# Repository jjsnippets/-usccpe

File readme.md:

# BSCPE USC Code Compilation

This repository cotains all the code and laboratory exercises that I did throughout my Bachelor of Computer Engineering Degree in the University of San Carlos.

*These were originally in separate repositories, but is merged for the convenience of everyone 😅.*

> **Contains the following subrepositories**:
>
> **CPE 1102L**: PROGRAMMING LOGIC AND DESIGN
> **CPE 1202L**: DATA STRUCTURES AND ALGORITHMS
> **CPE 2101L**: OBJECT ORIENTED PROGRAMMING
> **CPE 2201**: SOFTWARE DESIGN
> **CPE 3101L**: INTRODUCTION TO HDL
> **CPE 3102**: FEEDBACK AND CONTROL SYSTEMS
> **CPE 3103**: FUNDAMENTALS OF MIXED SIGNALS AND SENSORS
> **CPE 3104**: MICROPROCESSORS
> **CPE 3108**: NUMERICAL METHODS
> **CPE 3108**: INFORMATION ENGINEERING 1
> **CPE 3201**: EMBEDDED SYSTEMS
> **CPE 3203**: DIGITAL SIGNAL PROCESSING
> **CPE 3205**: EMERGING TECHNOLOGIES IN CPE
> **CPE 3252**: INFORMATION ENGINEERING 2
>
> Each contains its own brief readme.md.

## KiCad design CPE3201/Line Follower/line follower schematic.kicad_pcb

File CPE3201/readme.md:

# CPE 3201 (EMBEDDED SYSTEMS)
- All code is in C
- Hardware used: PIC16F877A microcontroller
- Compiler used: MPLAB XC8 v1.33

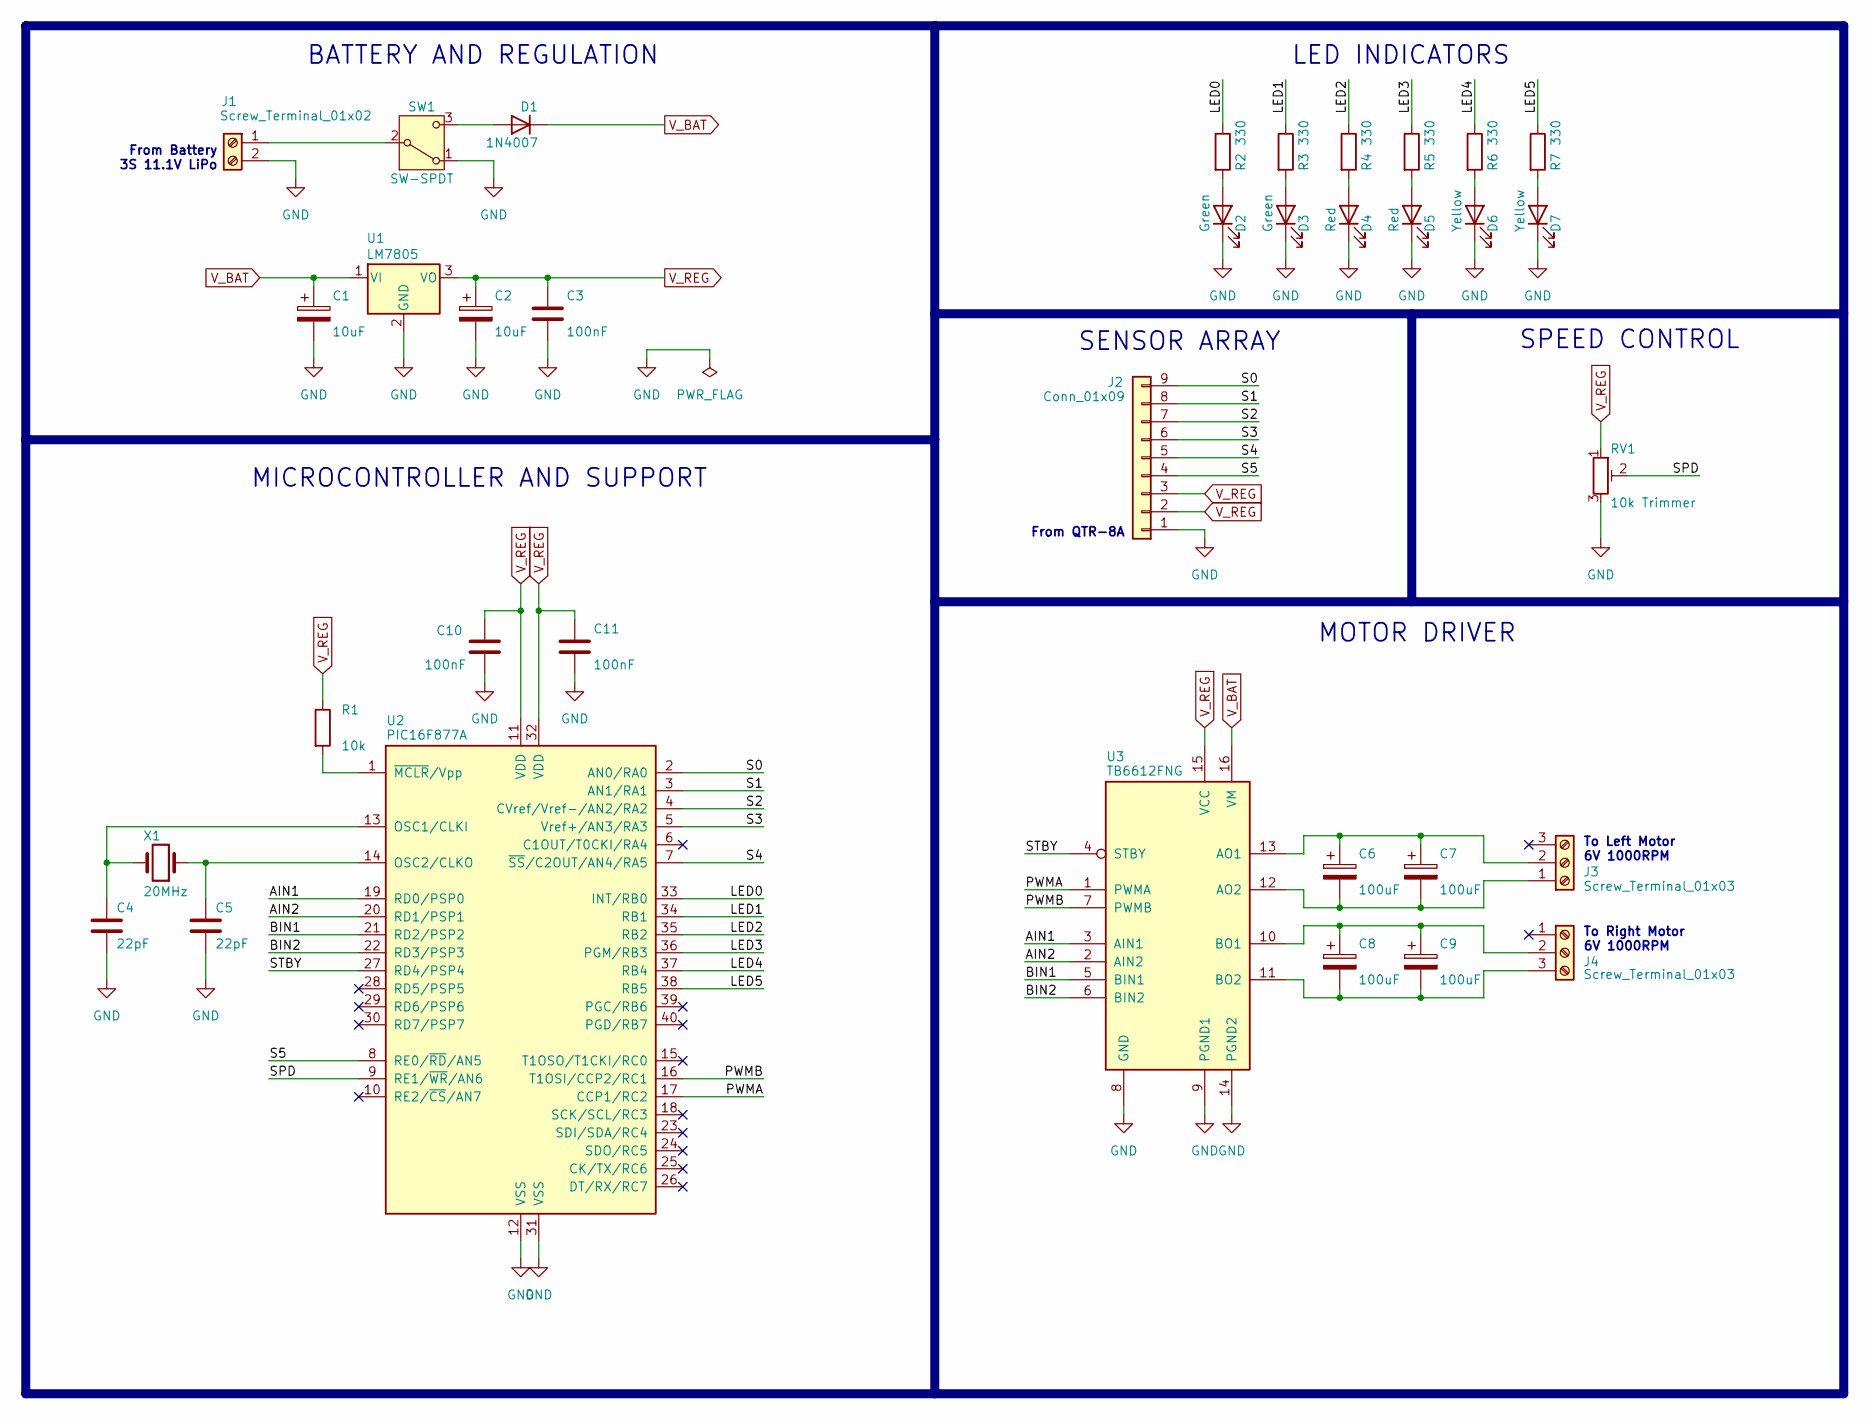
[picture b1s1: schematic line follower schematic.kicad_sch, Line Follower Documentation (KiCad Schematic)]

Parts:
C1, C2: 10uF; CP_Radial_D5.0mm_P2.50mm
C3, C10, C11: 100nF; C_Disc_D5.1mm_W3.2mm_P5.00mm
C4, C5: 22pF; C_Disc_D5.1mm_W3.2mm_P5.00mm
C6, C7, C8, C9: 100uF; CP_Radial_D6.3mm_P2.50mm
D1: 1N4007; D_DO-41_SOD81_P10.16mm_Horizontal
D2, D3: Green; LED_D5.0mm
D4, D5: Red; LED_D5.0mm
D6, D7: Yellow; LED_D5.0mm
J1: Screw_Terminal_01x02; TerminalBlock_Phoenix_MKDS-1,5-2-5.08_1x02_P5.08mm_Horizont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
J2: Conn_01x09; PinHeader_1x09_P2.54mm_Vertical
J3, J4: Screw_Terminal_01x03; TerminalBlock_Phoenix_MKDS-1,5-3_1x03_P5.00mm_Horizontal
R1: 10k; R_Axial_DIN0207_L6.3mm_D2.5mm_P10.16mm_Horizontal
R2, R3, R4, R5, R6, R7: 330; R_Axial_DIN0207_L6.3mm_D2.5mm_P10.16mm_Horizontal
RV1: 10k Trimmer; Potentiometer_Bourns_3296Y_Vertical
SW1: SW-SPDT; TerminalBlock_Phoenix_MKDS-1,5-3_1x03_P5.00mm_Horizontal
U1: LM7805; TO-220-3_Vertical
U2: PIC16F877A; DIP-40_W15.24mm
U3: TB6612FNG; DIP-16_W7.62mm_LongPads
X1: 20MHz; Crystal_HC49-U_Vertical

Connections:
/AIN1: U2.19 (RD0/PSP0), U3.3 (AIN1)
/AIN2: U2.20 (RD1/PSP1), U3.2 (AIN2)
/BIN1: U2.21 (RD2/PSP2), U3.5 (BIN1)
/BIN2: U2.22 (RD3/PSP3), U3.6 (BIN2)
/LED0: R2.1, U2.33 (INT/RB0)
/LED1: R3.1, U2.34 (RB1)
/LED2: R4.1, U2.35 (RB2)
/LED3: R5.1, U2.36 (PGM/RB3)
/LED4: R6.1, U2.37 (RB4)
/LED5: R7.1, U2.38 (RB5)
/PWMA: U2.17 (CCP1/RC2), U3.1 (PWMA)
/PWMB: U2.16 (T1OSI/CCP2/RC1), U3.7 (PWMB)
/S0: J2.9, U2.2 (AN0/RA0)
/S1: J2.8, U2.3 (AN1/RA1)
/S2: J2.7, U2.4 (CVref/Vref-/AN2/RA2)
/S3: J2.6, U2.5 (Vref+/AN3/RA3)
/S4: J2.5, U2.7 (~SS/C2OUT/AN4/RA5)
/S5: J2.4, U2.8 (RE0/~RD/AN5)
/SPD: RV1.2, U2.9 (RE1/~WR/AN6)
/STBY: U2.27 (RD4/PSP4), U3.4 (STBY)
GND: C1.2, C2.2, C3.2, C4.2, C5.2, C10.2, C11.2, D2.1 (K), D3.1 (K), D4.1 (K), D5.1 (K), D6.1 (K), D7.1 (K), J1.2, J2.1, RV1.3, SW1.1 (A), U1.2 (GND), U2.12 (VSS), U2.31 (VSS), U3.8 (GND), U3.9 (PGND1), U3.14 (PGND2)
unnamed: D1.2 (A), SW1.3 (C)
unnamed: D2.2 (A), R2.2
unnamed: D3.2 (A), R3.2
unnamed: D4.2 (A), R4.2
unnamed: D5.2 (A), R5.2
unnamed: D6.2 (A), R6.2
unnamed: D7.2 (A), R7.2
unnamed: J1.1, SW1.2 (B)
unnamed: C6.2, C7.2, J3.1, U3.12 (AO2)
unnamed: C6.1, C7.1, J3.2, U3.13 (AO1)
unnamed: C8.1, C9.1, J4.2, U3.10 (BO1)
unnamed: C8.2, C9.2, J4.3, U3.11 (BO2)
unnamed: C4.1, U2.13 (OSC1/CLKI), X1.2
unnamed: C5.1, U2.14 (OSC2/CLKO), X1.1
unnamed: R1.2, U2.1 (~MCLR/Vpp)
V_BAT: C1.1, D1.1 (K), U1.1 (VI), U3.16 (VM)
V_REG: C2.1, C3.1, C10.1, C11.1, J2.2, J2.3, R1.1, RV1.1, U1.3 (VO), U2.11 (VDD), U2.32 (VDD), U3.15 (VCC)

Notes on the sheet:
To Right Motor 6V 1000RPM
SPEED CONTROL
To Left Motor 6V 1000RPM
SENSOR ARRAY
BATTERY AND REGULATION
From Battery 3S 11.1V LiPo
LED INDICATORS
From QTR-8A
MICROCONTROLLER AND SUPPORT
MOTOR DRIVER

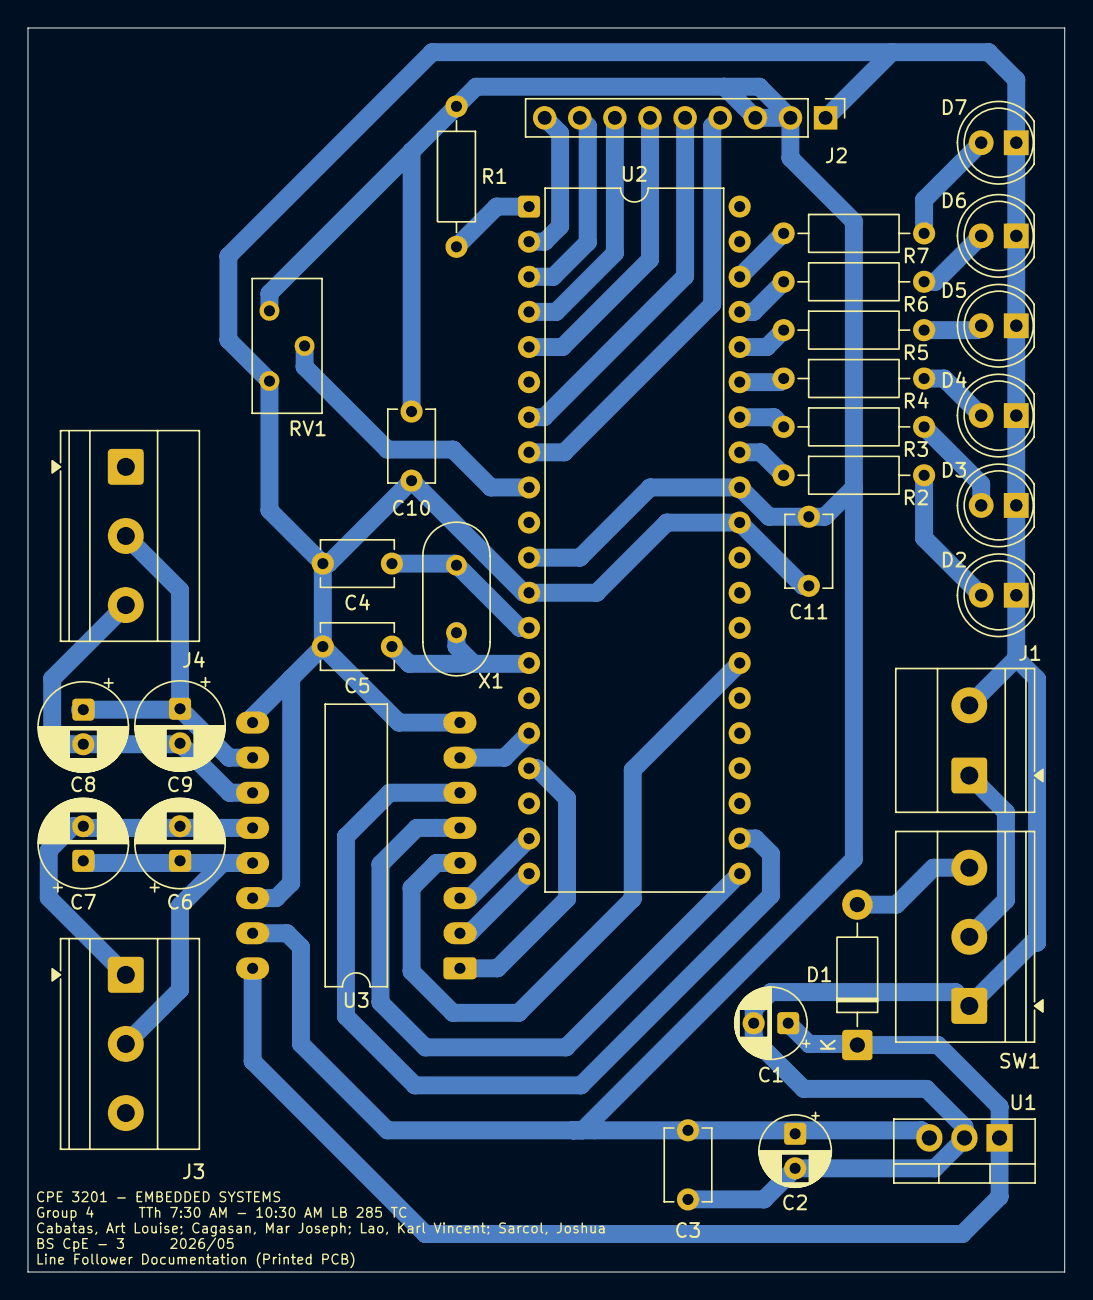
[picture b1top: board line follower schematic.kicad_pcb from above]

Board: 2 copper layers, 75.0 x 90.0 mm, 35 parts (0 on the bottom side), 38 nets.
